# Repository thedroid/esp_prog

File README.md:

# ESP8266 Programmer
A extension for the [`esptool`](https://github.com/themadinventor/esptool) originally written by Fredrik Ahlberg. The tool now enters the boot-loader mode w/o the need of a user interaction.

# Folders

## esptool
Modified version of the original tool.

## schematic
Required hardware

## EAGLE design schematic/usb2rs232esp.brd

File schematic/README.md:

# Hardware

In order to enter the bootloader GPIO0 needs to be low at system start. Before the regular programming/flashing is taking place, the modified `esptool` ensures that by using the spare RTS and DTR lines of the serial port. 
A reset is carried out by the RTS line while GPIO0 is held low via the DTR line.

Note that, we silently assume that GPIO2 and GPIO15 are pulled high during system start.

# Wiring

## Diagram

FTDI |Connection| ESP8266 | Note
:-----:|:----------:|:---------:|------
TX   |   ----   | RX      |
RX   |   ----   | TX      | 
RTS  | 220Ohm | Reset   | see considerations
DTR  | 220Ohm | GPIO0   | see considerations
Vio  | 56Ohm | Vdd     | Optional. Vio can alternativly be connected to 3.3Vout of the FTDI. Just ensure 3.3V levels.
GND  |   ----   | Vss     |

## Considerations
Open-drain output for DTR/RTS would be ideal for a true In System Programmer (ISP). In dormant state they would leave the actual circuit unaffected. However, the lines are active low. Meaning that during inactivity the lines are high. A double inverting MOSFET stage would be required to accomplish the desired behavior. As the same issues holds for the TX line I currently decided to go with the simple and cheap solution: resistors. The more advanced solution would be a driver IC which switches RTS, DTR, and TX into a Tri-Z state. The driver could be controlled by the DTR line.

## Pinout

The ESP-03/4 has the most GPIO pins. Thus, it is most likely that the majority of the people actively developing code for this chip will use this model and its specific pin configuration. 
The following pinout of the ISP is optimized for the usage of the ESP-03/4 board on top of a single sided PCB. A 6 pin (3x2) SMD header can easily be routed w/o intersections. Making it perfect for low-cost home-echted PCBs.
 
Pin header on the PCB (top view):

Description |   |   | Description
------------:|:---:|:---:|:------------
Vss         | 1 | 2 | Tx
Rx          | 3 | 4 | /Reset
Vdd         | 5 | 6 | GPIO0

Note that, for the ISP cable the RX/TX lines need to be twisted.

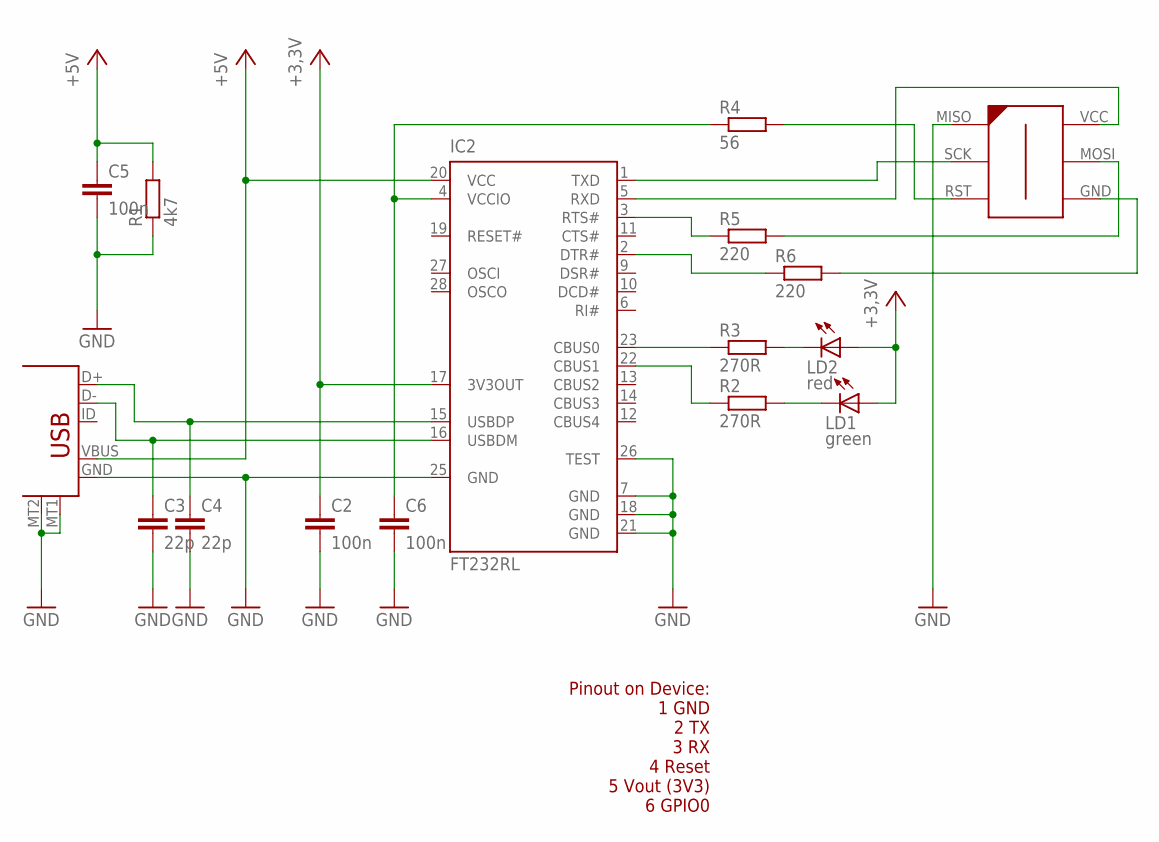
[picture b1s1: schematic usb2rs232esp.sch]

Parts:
C2, C5, C6: 100n; C0603
C3, C4: 22p; C0603
IC2: FT232RL; SSOP28
LD1: green; CHIP-LED0603
LD2: red; CHIP-LED0603
R1: 4k7; R0603
R2, R3: 270R; R0603
R4: 56; R0603
R5, R6: 220; R0603
U$3: AVR-ISP-6-EDGE; 6PAD_ISP
U$40: USB-B; USB-MICROB

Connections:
+3,3V: C2.1, IC2.17 (3V3OUT), LD1.A, LD2.A
+5V: C5.1, IC2.20 (VCC), R1.2, U$40.VBUS
GND: C2.2, C3.2, C4.2, C5.2, C6.2, IC2.7 (GND), IC2.18 (GND), IC2.21 (GND), IC2.25 (GND), IC2.26 (TEST), R1.1, U$3.MISO, U$40.GND, U$40.MT1, U$40.MT2
unnamed: IC2.23 (CBUS0), R3.1
unnamed: IC2.22 (CBUS1), R2.1
unnamed: C4.1, IC2.15 (USBDP), U$40.D+
unnamed: C3.1, IC2.16 (USBDM), U$40.D-
unnamed: C6.1, IC2.4 (VCCIO), R4.1
unnamed: LD1.C, R2.2
unnamed: LD2.C, R3.2
unnamed: R4.2, U$3.RST
unnamed: R5.2, U$3.MOSI
unnamed: R6.2, U$3.GND
unnamed: IC2.5 (RXD), U$3.VCC
unnamed: IC2.1 (TXD), U$3.SCK
unnamed: IC2.3 (RTS#), R5.1
unnamed: IC2.2 (DTR#), R6.1

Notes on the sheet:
Pinout on Device: 1 GND 2 TX 3 RX 4 Reset 5 Vout (3V3) 6 GPIO0

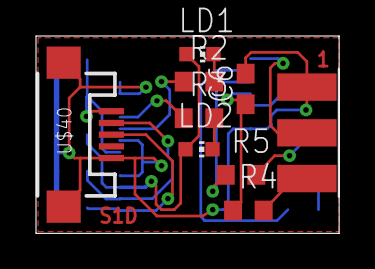
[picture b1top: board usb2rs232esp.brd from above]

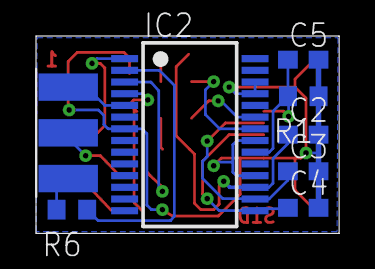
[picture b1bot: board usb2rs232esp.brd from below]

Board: 2 copper layers, 16.8 x 11.0 mm, 16 parts (7 on the bottom side), 17 nets.

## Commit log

2014-10-25 Initial commit
    -Moved esptool into dedicated directory
    -Intoduced schematics
2014-10-25 Automated bootloader entry
2014-10-25 README introduced
2014-10-25 typo
2014-10-25 init
2014-10-25 improved docu
2014-10-25 improved lables
2014-12-28 reverted readme.md
